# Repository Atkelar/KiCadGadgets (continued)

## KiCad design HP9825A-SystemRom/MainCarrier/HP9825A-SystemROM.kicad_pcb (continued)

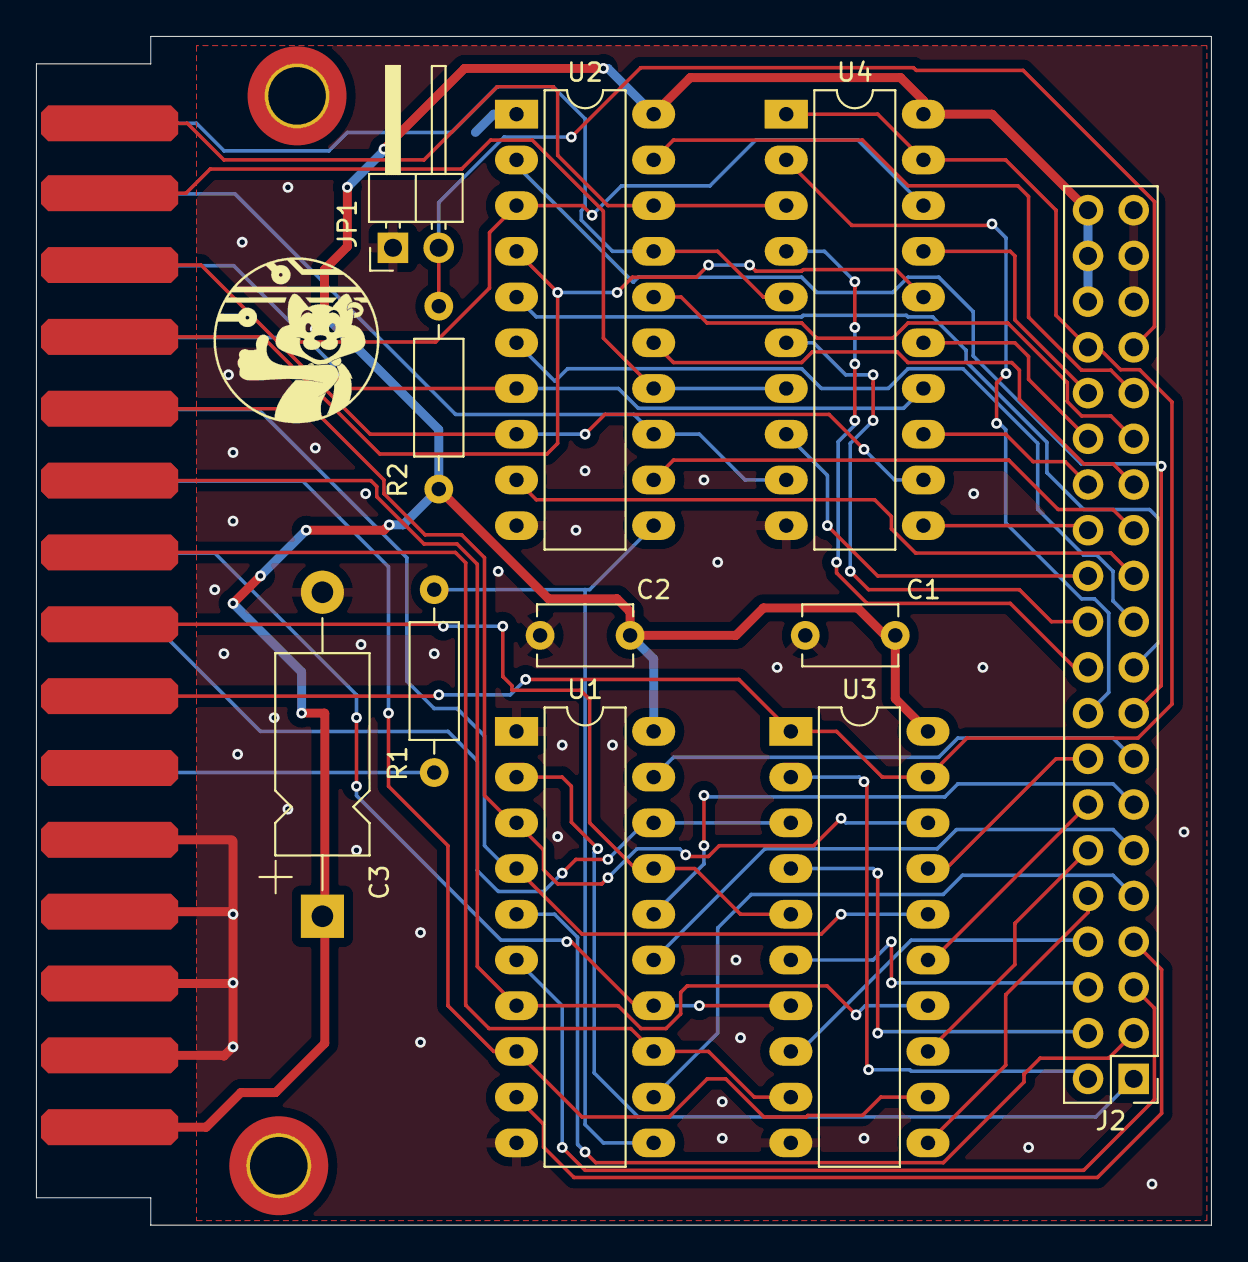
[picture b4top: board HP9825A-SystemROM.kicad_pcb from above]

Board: 2 copper layers, 65.3 x 66.0 mm, 12 parts (0 on the bottom side), 54 nets.

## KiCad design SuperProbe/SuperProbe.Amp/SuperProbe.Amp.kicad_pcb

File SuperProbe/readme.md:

# Superprobe

This is my take (PCB) on the Superprobe schematics that Mr Carlson published in one of his videos. It is based on THT rather than SMD parts, becuase that's what I had. The layout also fits a 20mm copper heating pipe which is common around here.

## Exports

The provided ZIP files should((have not tested!)) be proper for direct ordering form jlcpcb; please use at your own risk and be sure to validate when ordering!

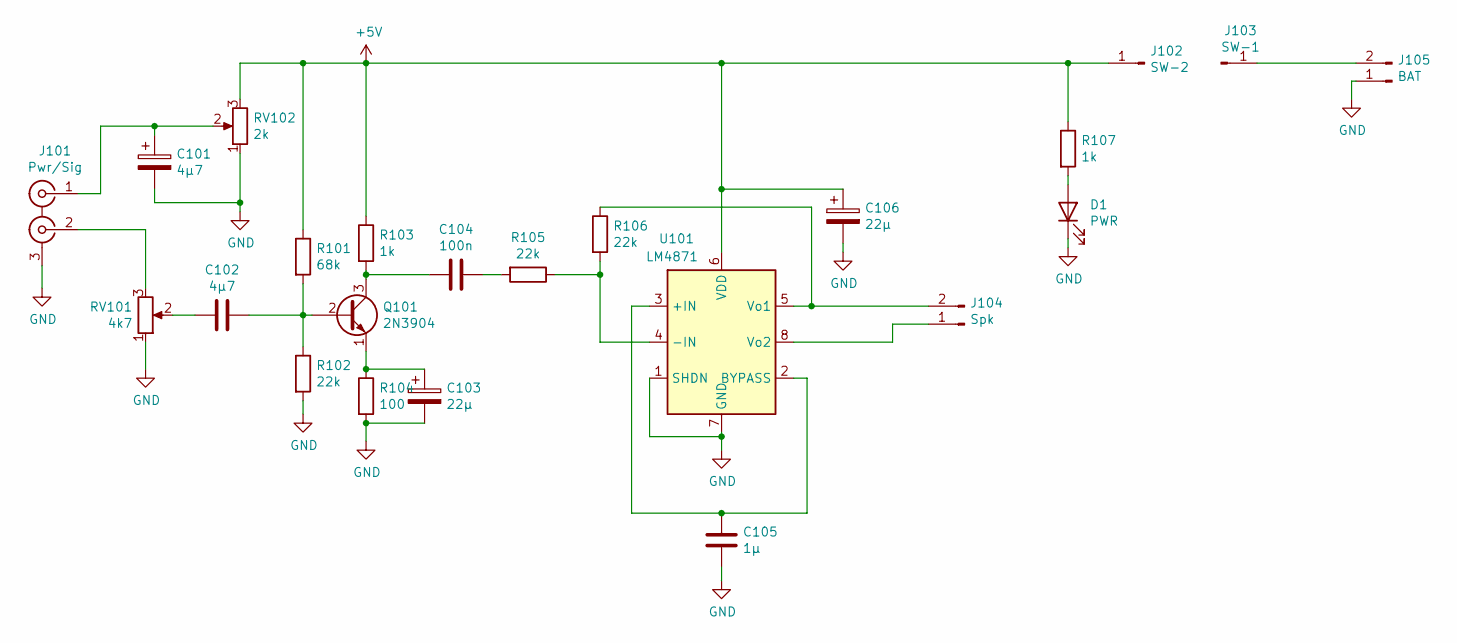
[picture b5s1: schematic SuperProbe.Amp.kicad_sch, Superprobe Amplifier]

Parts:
C101: 4µ7; CP_Radial_Tantal_D5.5mm_P5.00mm
C102: 4µ7; C_Disc_D5.0mm_W2.5mm_P5.00mm
C103, C106: 22µ; CP_Radial_Tantal_D5.5mm_P5.00mm
C104: 100n; C_Disc_D5.0mm_W2.5mm_P5.00mm
C105: 1µ; C_Disc_D5.0mm_W2.5mm_P5.00mm
D1: PWR; LED_D5.0mm
J101: Pwr/Sig; PinHeader_1x03_P2.54mm_Vertical
J102: SW-2; TestPoint_THTPad_2.5x2.5mm_Drill1.2mm
J103: SW-1; TestPoint_THTPad_2.5x2.5mm_Drill1.2mm
J104: Spk; PinHeader_1x02_P2.54mm_Vertical
J105: BAT; PinHeader_1x02_P2.54mm_Vertical
Q101: 2N3904; TO-92_Inline
R101: 68k; R_Axial_DIN0309_L9.0mm_D3.2mm_P12.70mm_Horizontal
R102, R105, R106: 22k; R_Axial_DIN0309_L9.0mm_D3.2mm_P12.70mm_Horizontal
R103, R107: 1k; R_Axial_DIN0309_L9.0mm_D3.2mm_P12.70mm_Horizontal
R104: 100; R_Axial_DIN0309_L9.0mm_D3.2mm_P12.70mm_Horizontal
RV101: 4k7; Potentiometer_Alps_RK163_Single_Horizontal
RV102: 2k; Potentiometer_Alps_RK163_Single_Horizontal
U101: LM4871; SOIC-8_3.9x4.9mm_P1.27mm

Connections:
+5V: C106.1, J102.1, R101.1, R103.1, R107.1, RV102.3, U101.6 (VDD)
GND: C101.2, C103.2, C105.1, C106.2, D1.1 (K), J101.3 (EXT), J105.1, R102.2, R104.2, RV101.1, RV102.1, U101.1 (SHDN), U101.7 (GND)
unnamed: C101.1, J101.1 (IN1), RV102.2
unnamed: C102.1, Q101.2 (B), R101.2, R102.1
unnamed: C102.2, RV101.2
unnamed: C103.1, Q101.1 (E), R104.1
unnamed: C104.1, R105.2
unnamed: C104.2, Q101.3 (C), R103.2
unnamed: C105.2, U101.2 (BYPASS), U101.3 (+IN)
unnamed: D1.2 (A), R107.2
unnamed: J101.2 (IN2), RV101.3
unnamed: J103.1, J105.2
unnamed: J104.1, U101.8 (Vo2)
unnamed: J104.2, R106.1, U101.5 (Vo1)
unnamed: R105.1, R106.2, U101.4 (-IN)

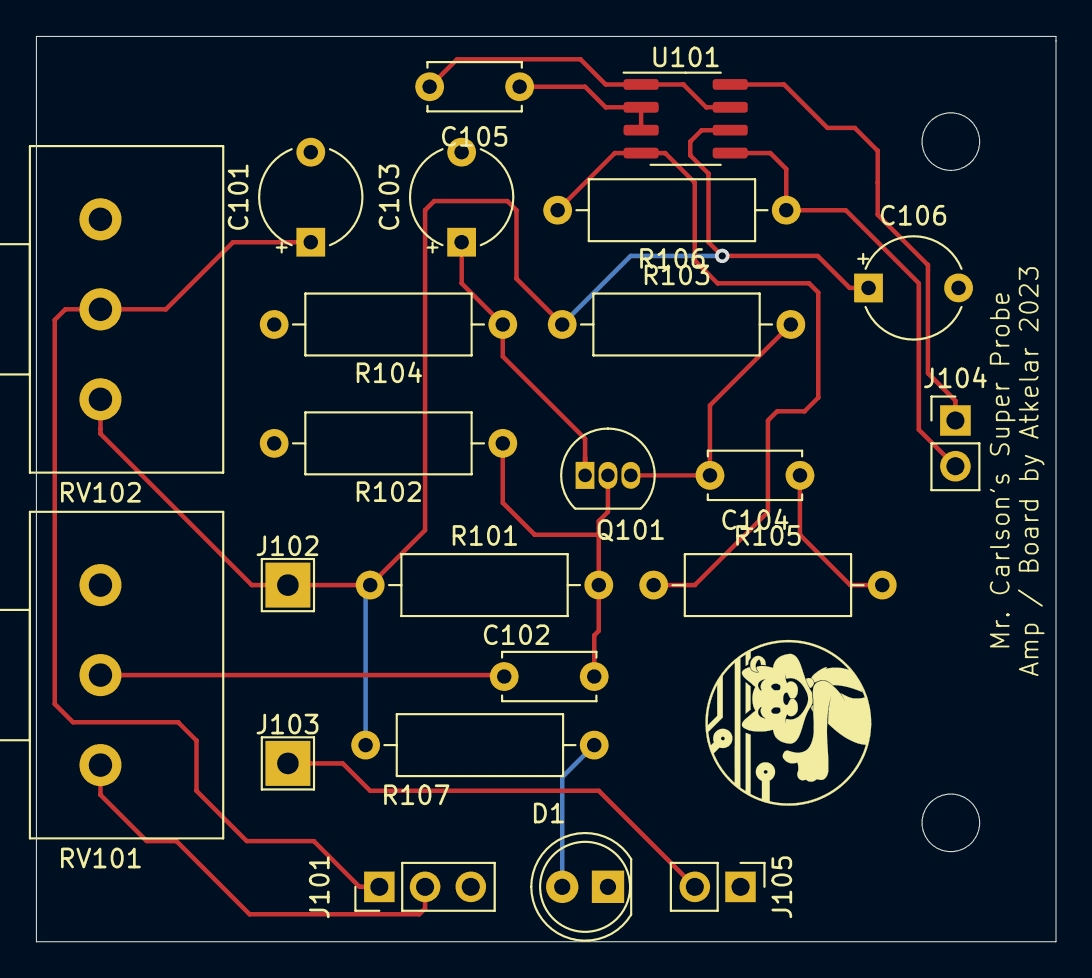
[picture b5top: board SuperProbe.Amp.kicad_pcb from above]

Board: 2 copper layers, 56.6 x 50.3 mm, 23 parts (0 on the bottom side), 15 nets.

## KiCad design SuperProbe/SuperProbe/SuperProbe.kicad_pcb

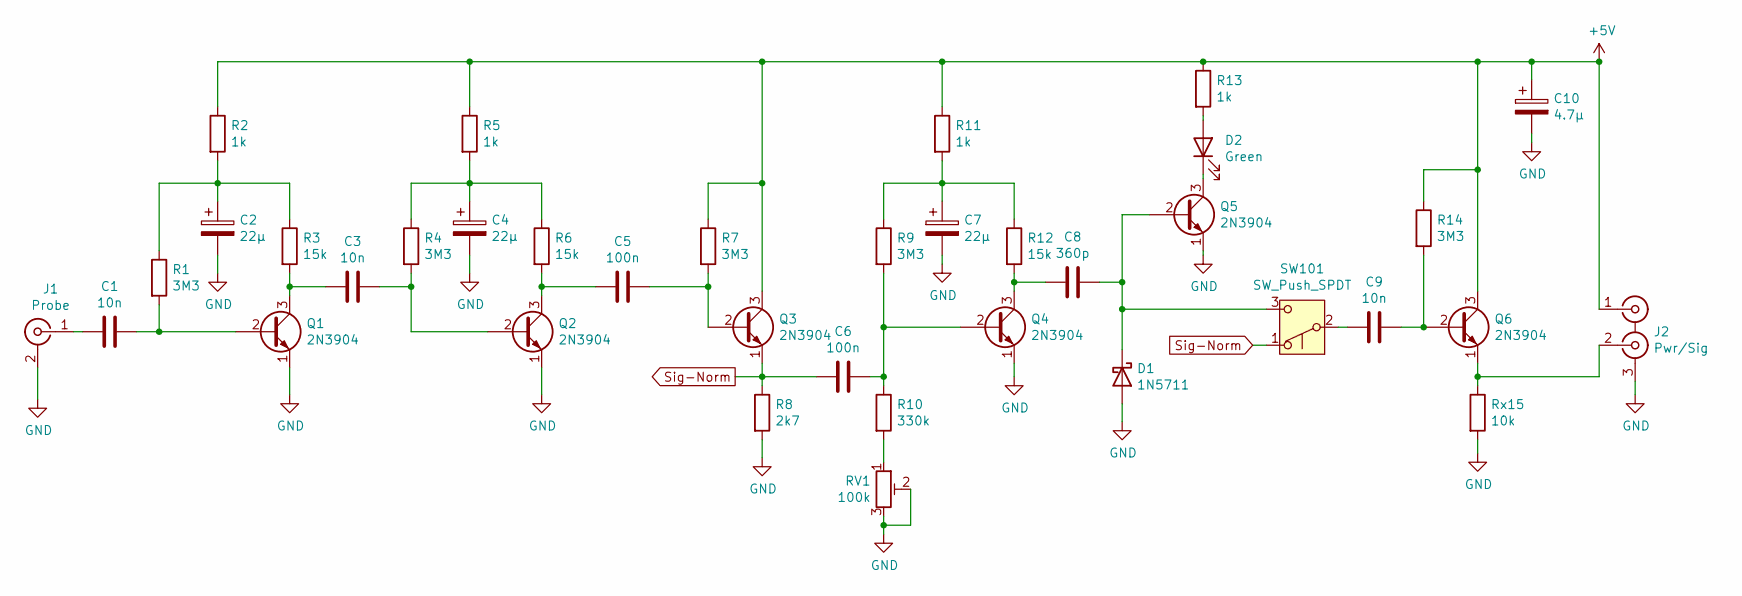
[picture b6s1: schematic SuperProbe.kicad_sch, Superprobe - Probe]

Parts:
C1, C3, C9: 10n; C_Disc_D3.8mm_W2.6mm_P2.50mm
C2, C4, C7: 22µ; CP_Radial_Tantal_D5.5mm_P5.00mm
C5, C6: 100n; C_Disc_D5.0mm_W2.5mm_P5.00mm
C8: 360p; C_Disc_D3.8mm_W2.6mm_P2.50mm
C10: 4.7µ; CP_Radial_Tantal_D5.5mm_P5.00mm
D1: 1N5711; D_DO-35_SOD27_P2.54mm_Vertical_AnodeUp
D2: Green; PinHeader_1x02_P2.54mm_Vertical
J1: Probe; SolderWirePad_1x02_P3.81mm_Drill1mm
J2: Pwr/Sig; PinHeader_1x03_P2.54mm_Horizontal
Q1, Q2, Q3, Q4, Q5, Q6: 2N3904; TO-92_Inline
R1, R4, R7, R9, R14: 3M3; R_Axial_DIN0207_L6.3mm_D2.5mm_P7.62mm_Horizontal
R2, R5, R11, R13: 1k; R_Axial_DIN0207_L6.3mm_D2.5mm_P7.62mm_Horizontal
R3, R6, R12: 15k; R_Axial_DIN0207_L6.3mm_D2.5mm_P7.62mm_Horizontal
R8: 2k7; R_Axial_DIN0207_L6.3mm_D2.5mm_P7.62mm_Horizontal
R10: 330k; R_Axial_DIN0207_L6.3mm_D2.5mm_P7.62mm_Horizontal
RV1: 100k; Potentiometer_Bourns_3299P_Horizontal
Rx15: 10k; R_Axial_DIN0207_L6.3mm_D2.5mm_P7.62mm_Horizontal
SW101: SW_Push_SPDT; SW_Slide_1P2T_CK_OS102011MS2Q

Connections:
+5V: C10.1, J2.1 (IN1), Q3.3 (C), Q6.3 (C), R2.1, R5.1, R7.1, R11.1, R13.1, R14.1
GND: C2.2, C4.2, C7.2, C10.2, D1.2 (A), J1.2 (Ext), J2.3 (EXT), Q1.1 (E), Q2.1 (E), Q4.1 (E), Q5.1 (E), R8.2, RV1.2, RV1.3, Rx15.2
unnamed: C1.1, Q1.2 (B), R1.2
unnamed: C1.2, J1.1 (In)
unnamed: C2.1, R1.1, R2.2, R3.1
unnamed: C3.1, Q2.2 (B), R4.2
unnamed: C3.2, Q1.3 (C), R3.2
unnamed: C4.1, R4.1, R5.2, R6.1
unnamed: C5.1, Q3.2 (B), R7.2
unnamed: C5.2, Q2.3 (C), R6.2
unnamed: C6.1, Q4.2 (B), R9.2, R10.1
unnamed: C7.1, R9.1, R11.2, R12.1
unnamed: C8.1, D1.1 (K), Q5.2 (B), SW101.3 (C)
unnamed: C8.2, Q4.3 (C), R12.2
unnamed: C9.1, Q6.2 (B), R14.2
unnamed: C9.2, SW101.2 (B)
unnamed: D2.1 (K), Q5.3 (C)
unnamed: D2.2 (A), R13.2
unnamed: J2.2 (IN2), Q6.1 (E), Rx15.1
unnamed: R10.2, RV1.1
Sig-Norm: C6.2, Q3.1 (E), R8.1, SW101.1 (A)

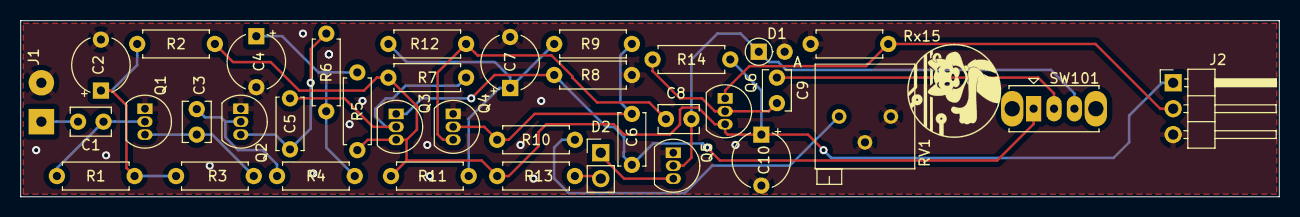
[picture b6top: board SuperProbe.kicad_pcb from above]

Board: 2 copper layers, 123.4 x 17.3 mm, 37 parts (0 on the bottom side), 21 nets.

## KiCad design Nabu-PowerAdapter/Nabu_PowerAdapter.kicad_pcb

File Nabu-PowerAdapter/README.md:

# Nabu Power Supply Adapter

This adapter goes between a "TOP 60522" open frame power supply and the Nabu mainboard to give an easy and straightforward replacement for the built in power supply; the new one runs on multi voltages. 

Be sure to double check for correct voltages before plugging the mainboard in again!

There is also a jumper connector to connect a 12V DC fan if needed.

The "TOP 60522" has minimum current requirements for proper regulation, so depending on tolerances it might need a load resistor; mine didn't, but I can update the cicuit to include one if needed...

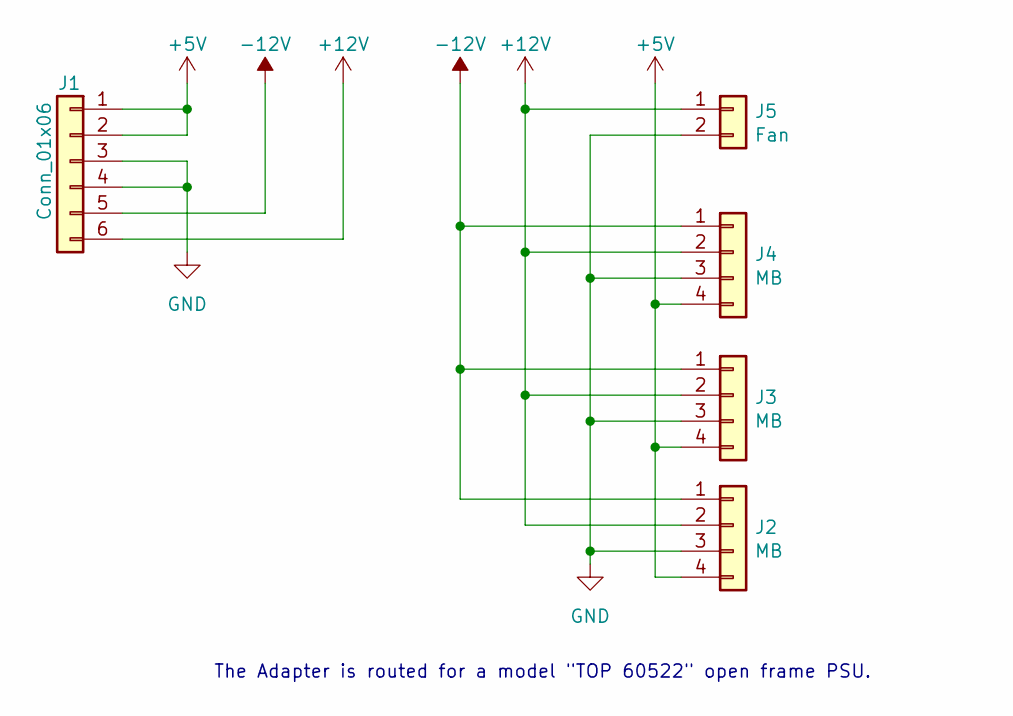
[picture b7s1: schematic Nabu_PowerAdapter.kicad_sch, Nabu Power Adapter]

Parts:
J1: Conn_01x06; PhoenixContact_MCV_1,5_6-G-3.81_1x06_P3.81mm_Vertical
J2, J3, J4: MB; PinHeader_1x04_P2.54mm_Horizontal
J5: Fan; PinHeader_1x02_P2.54mm_Vertical

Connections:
+5V: J1.1, J1.2, J2.4, J3.4, J4.4
+12V: J1.6, J2.2, J3.2, J4.2, J5.1
-12V: J1.5, J2.1, J3.1, J4.1
GND: J1.3, J1.4, J2.3, J3.3, J4.3, J5.2

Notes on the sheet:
The Adapter is routed for a model "TOP 60522" open frame PSU.

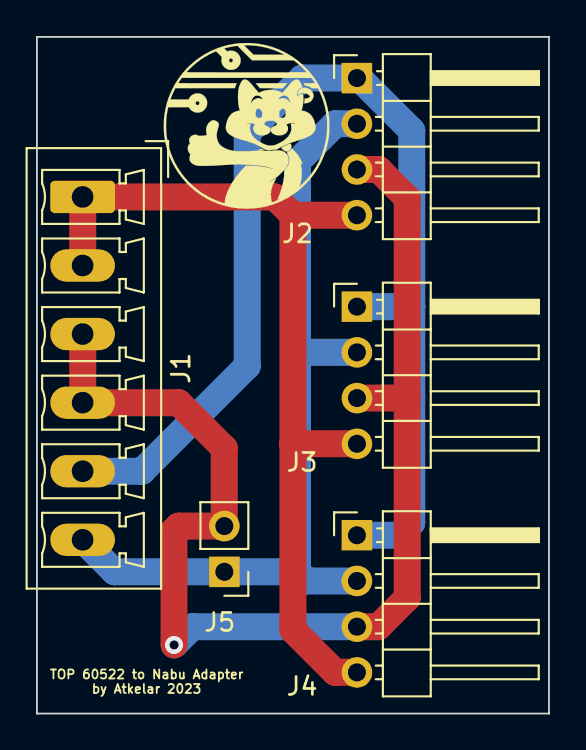
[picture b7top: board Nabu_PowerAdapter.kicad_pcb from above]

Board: 2 copper layers, 28.4 x 37.6 mm, 5 parts (0 on the bottom side), 4 nets.

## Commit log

2023-08-08 Created public versions
2023-08-13 Add power labels and upgrade project to KiCAD 7.0.1
2024-05-20 Create readme.md for Superprobe
2024-05-20 Added exported ZIP files
2024-05-20 Almost all files...
    Schematic file fials with 400 error
2024-05-20 Create SuperProbe.kicad_sch
    upload failed...?
2024-05-20 Amplifier, sans SCH file...
2026-01-17 Created base folder for ROM PCB
2026-01-17 Added Main PCB project
2026-01-17 Update readme.md
    Added a brief description
2026-04-13 Added initial (rev-B) RAM PCB
2026-05-05 Published first working version
2026-05-05 Update readme.md
    Added a picture of the success...
